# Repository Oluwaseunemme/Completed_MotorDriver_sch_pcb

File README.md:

# Completed_MotorDriver_sch_pcb
A few days ago, I shared the schematic for my custom 4-channel Arduino motor driver built around the 74HC595 shift register and L293D motor drivers. Today, I'm excited to share some progress—the design is now fully functional in simulation, and I've begun developing the software library that powers it.

🔹 From Hardware to Software

One of the goals of this project wasn't just to design the hardware, but to build a reusable and intuitive software interface for controlling it.

Instead of manually controlling each motor direction pin, the library uses bitwise operations to combine the direction of all four motors into a single 8-bit value. That byte is then transmitted to the 74HC595 using Arduino's shiftOut() function, updating all motor direction outputs simultaneously.

Each motor is represented using a simple 2-bit encoding:

• 10 → Forward
• 01 → Backward
• 00 → Stop

So, a binary value like:

10100110

contains the complete direction information for all four motors.

🔹 A Closer Look at the Logic

One part I particularly enjoyed implementing was the binary-to-byte conversion using bitwise operators.

value <<= 1;

if (strValue[i] == '1')
    value |= 1;

The left-shift operator (<<) moves the existing bits one position to the left, creating room for the next bit. The OR assignment operator (|=) then sets only the least significant bit when needed, without affecting the bits that have already been built.

It's a small piece of code, but it's a great reminder of how low-level bit manipulation directly translates into controlling real hardware.

🔹 Efficient GPIO Usage

By using the 74HC595 as a direction controller, the Arduino only needs three digital pins to control the direction of all four motors, regardless of how many outputs are driven by the shift register.

Meanwhile, each L293D enable pin is connected to a dedicated PWM pin, allowing independent speed control for every motor while keeping GPIO usage to a minimum.

This combination provides a clean separation between:

Direction control (Shift Register)
Speed control (PWM)
Power driving (L293D)

🔹 Current Progress

✅ 4 independent DC motor channels
✅ Individual PWM speed control
✅ Direction control through a single 74HC595 shift register
✅ Object-oriented Arduino driver library under development
✅ Successfully validated in Proteus simulation

🔹 What's Next?

The next phase is moving from simulation to a physical prototype, followed by refining the library to make it easier for anyone to integrate the driver into robotics and embedded projects.

Projects like this continue to remind me that embedded systems are where software and hardware truly meet. A few lines of C++ and some bitwise operations eventually become electrical signals that move real motors—and that's one of the most rewarding parts of embedded engineering.

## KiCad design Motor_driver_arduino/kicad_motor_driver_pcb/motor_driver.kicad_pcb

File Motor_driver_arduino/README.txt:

A few days ago, I shared the schematic for my custom 4-channel Arduino motor driver built around the 74HC595 shift register and L293D motor drivers. Today, I'm excited to share some progress—the design is now fully functional in simulation, and I've begun developing the software library that powers it.

🔹 From Hardware to Software

One of the goals of this project wasn't just to design the hardware, but to build a reusable and intuitive software interface for controlling it.

Instead of manually controlling each motor direction pin, the library uses bitwise operations to combine the direction of all four motors into a single 8-bit value. That byte is then transmitted to the 74HC595 using Arduino's shiftOut() function, updating all motor direction outputs simultaneously.

Each motor is represented using a simple 2-bit encoding:

• 10 → Forward
• 01 → Backward
• 00 → Stop

So, a binary value like:

10100110

contains the complete direction information for all four motors.

🔹 A Closer Look at the Logic

One part I particularly enjoyed implementing was the binary-to-byte conversion using bitwise operators.

value <<= 1;

if (strValue[i] == '1')
    value |= 1;

The left-shift operator (<<) moves the existing bits one position to the left, creating room for the next bit. The OR assignment operator (|=) then sets only the least significant bit when needed, without affecting the bits that have already been built.

It's a small piece of code, but it's a great reminder of how low-level bit manipulation directly translates into controlling real hardware.

🔹 Efficient GPIO Usage

By using the 74HC595 as a direction controller, the Arduino only needs three digital pins to control the direction of all four motors, regardless of how many outputs are driven by the shift register.

Meanwhile, each L293D enable pin is connected to a dedicated PWM pin, allowing independent speed control for every motor while keeping GPIO usage to a minimum.

This combination provides a clean separation between:

Direction control (Shift Register)
Speed control (PWM)
Power driving (L293D)

🔹 Current Progress

✅ 4 independent DC motor channels
✅ Individual PWM speed control
✅ Direction control through a single 74HC595 shift register
✅ Object-oriented Arduino driver library under development
✅ Successfully validated in Proteus simulation

🔹 What's Next?

The next phase is moving from simulation to a physical prototype, followed by refining the library to make it easier for anyone to integrate the driver into robotics and embedded projects.

Projects like this continue to remind me that embedded systems are where software and hardware truly meet. A few lines of C++ and some bitwise operations eventually become electrical signals that move real motors—and that's one of the most rewarding parts of embedded engineering.

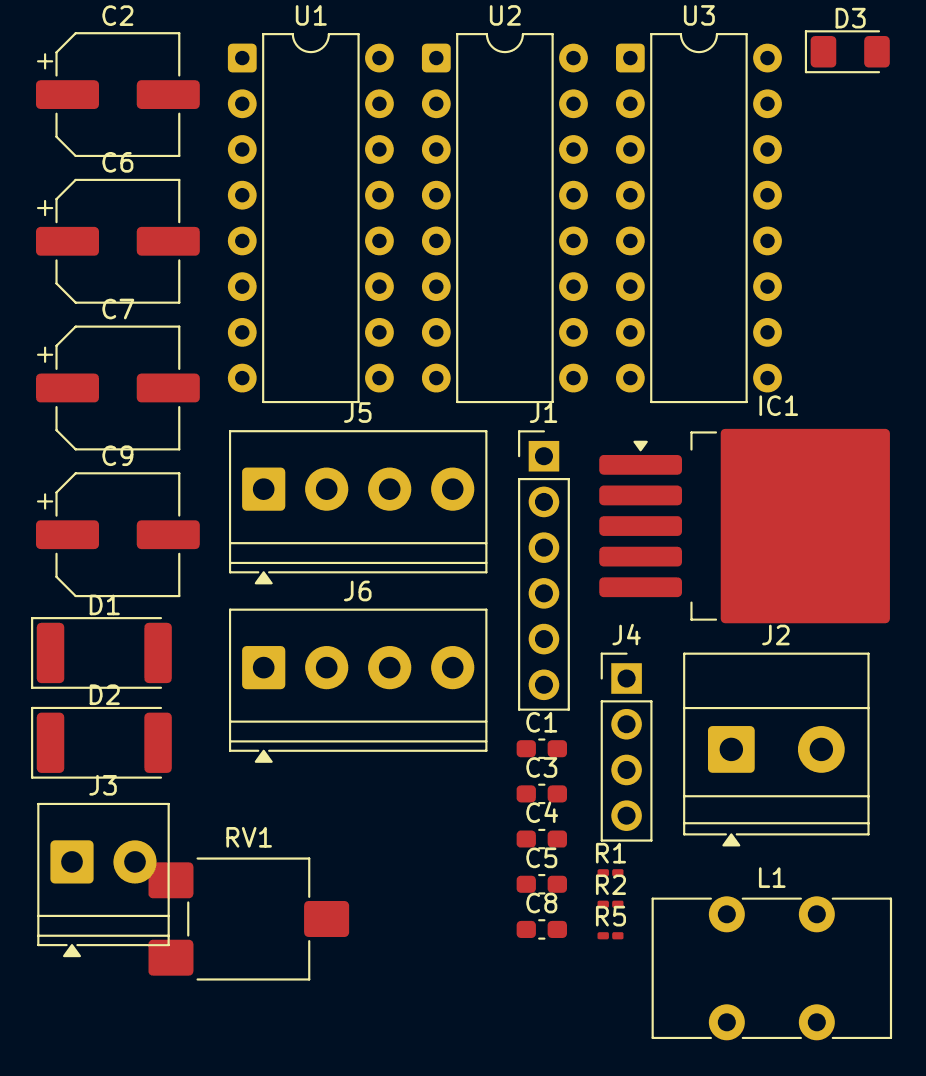
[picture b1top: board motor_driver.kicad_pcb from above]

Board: 2 copper layers, 27 parts (0 on the bottom side), 35 nets, no tracks yet.

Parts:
C1, C3, C4, C5: 100nf; C_0603_1608Metric_Pad1.08x0.95mm_HandSolder
C2, C6, C7: 20uf; CP_Elec_6.3x5.4
C8: 0.15uf; C_0603_1608Metric_Pad1.08x0.95mm_HandSolder
C9: 2000uf; CP_Elec_6.3x5.4
D1, D2: LED; LED_2512_6332Metric_Pad1.52x3.35mm_HandSolder
D3: 1N5821; D_1206_3216Metric_Pad1.42x1.75mm_HandSolder
IC1: LM2577; TO-263-5_TabPin3
J1: Conn_01x06_Pin; PinHeader_1x06_P2.54mm_Vertical
J2: Motor/load supply; TerminalBlock_Phoenix_MKDS-1,5-2_1x02_P5.00mm_Horizontal
J3: chip supply +5v; TerminalBlock_Phoenix_PT-1,5-2-3.5-H_1x02_P3.50mm_Horizontal
J4: Conn_01x04_Pin; PinHeader_1x04_P2.54mm_Vertical
J5: M1/M2; TerminalBlock_Phoenix_PT-1,5-4-3.5-H_1x04_P3.50mm_Horizontal
J6: M3/M4; TerminalBlock_Phoenix_PT-1,5-4-3.5-H_1x04_P3.50mm_Horizontal
L1: L_Ferrite; L_CommonMode_Toroid_Vertical_L13.0mm_W7.5mm_Px6.00mm_Py5.00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
R1: 500; R_0201_0603Metric_Pad0.64x0.40mm_HandSolder
R2: 1k; R_0201_0603Metric_Pad0.64x0.40mm_HandSolder
R5: 2.2k; R_0201_0603Metric_Pad0.64x0.40mm_HandSolder
RV1: 10k; Potentiometer_ACP_CA6-VSMD_Vertical
U1, U3: L293D; DIP-16_W7.62mm
U2: 74HC595; DIP-16_W7.62mm

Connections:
GND: C2.2, C6.2, C7.2, C8.2, C9.2, D1.1 (K), D2.1 (K), IC1.3 (GND), J1.6, J2.2, J3.2, RV1.1, U1.4 (GND), U1.5 (GND), U1.12 (GND), U1.13 (GND), U2.8 (GND), U3.4 (GND), U3.5 (GND), U3.12 (GND), U3.13 (GND)
L1E1: J4.1, U1.1 (EN1,2)
L1E2: J4.2, U1.9 (EN3,4)
L2E1: J4.3, U3.1 (EN1,2)
L2E2: J4.4, U3.9 (EN3,4)
Lvcc: C6.1, J3.1, R1.1, U1.16 (VCC1), U2.16 (VCC), U3.16 (VCC1)
Mvc: C9.1, D3.1 (K), RV1.3, U1.8 (VCC2)
Mvcc: C2.1, C7.1, IC1.5 (VIN), J2.1, L1.1, R2.1, U3.8 (VCC2)
unnamed: C8.1, R5.2
unnamed: D1.2 (A), R2.2
unnamed: D2.2 (A), R1.2
unnamed: D3.2 (A), IC1.4 (VSW), L1.2
unnamed: IC1.1 (COMP), R5.1
unnamed: IC1.2 (FB), RV1.2
unnamed: J1.1, U2.14 (SER)
unnamed: J1.2, U2.11 (SRCLK)
unnamed: J1.3, U2.10 (~SRCLR)
unnamed: J1.4, U2.12 (RCLK)
unnamed: J1.5, U2.13 (~OE)
unnamed: C1.1, J5.1, U1.3 (1Y)
unnamed: C1.2, J5.2, U1.6 (2Y)
unnamed: C3.1, J5.3, U1.11 (3Y)
unnamed: C3.2, J5.4, U1.14 (4Y)
unnamed: C4.1, J6.1, U3.3 (1Y)
unnamed: C4.2, J6.2, U3.6 (2Y)
unnamed: C5.1, J6.3, U3.11 (3Y)
unnamed: C5.2, J6.4, U3.14 (4Y)
unnamed: U1.2 (1A), U2.15 (QA)
unnamed: U1.7 (2A), U2.1 (QB)
unnamed: U1.10 (3A), U2.2 (QC)
unnamed: U1.15 (4A), U2.3 (QD)
unnamed: U2.4 (QE), U3.2 (1A)
unnamed: U2.5 (QF), U3.7 (2A)
unnamed: U2.6 (QG), U3.10 (3A)
unnamed: U2.7 (QH), U3.15 (4A)

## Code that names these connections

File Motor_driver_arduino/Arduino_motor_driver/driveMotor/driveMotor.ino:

#include "Motor_class_opp.h"

motorDriver myDriver = motorDriver(LATCHPIN, CLOCKPIN, DATAPIN, L1E1, L1E2, L2E1, L2E2);

void setup(){
  myDriver.init();
  Serial.begin(9600);
}

bool isChange=true;
long interval=1000, lastime;
void loop(){
    //int m1Speed = map(analogRead(A0), 0, 1023, 0, 255);
    if(millis()-lastime>=interval){
      lastime=millis();
      //Serial.println("m1 speed:"+String(analogRead(A0)));
      myDriver.setSpeed(250, 100, 50, 250);
      myDriver.setDirection("backward", "forward", "backward", "forward");
     }
}
